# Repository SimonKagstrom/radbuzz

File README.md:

# Radbuzz
Radbuzz is an infotainment and trip computer for electric mopeds and motorcycles, targeting VESC-based
controllers. It's built for an ESP32P4 microcontroller, but can also be run on the desktop for testing.

<p align="center">

</p>
<p align="center">

</p>
<p align="center">

</p>
<p align="center">

</p>

Features:

* OpenStreetMap-based map (currently OpenCycleMap) with different zoom levels, via a GPS module
* Supports receiving Google maps/OsmAnd/etc navigation instructions via the [Gadgetbridge](https://github.com/Freeyourgadget/Gadgetbridge) app
* Speedometer, both based on VESC data and GPS
* Trip data, with average consumption, distance etc
* Tesla-style power meter bar on the right
* Trip log shown on the map, with power indicator in color
* Range estimation shown on the map
* BMS status via BLE (currently em3ev KingShark/Ali new energy BMSes)
* Incoming phone calls can accepted/declined
* SMS:es and emails are forwarded from the phone
* A menu for configuration
* Written in clean and modern C++ (C++23)

Hardware:

* [Waveshare 4.3" ESP32P4 Touch](https://www.waveshare.com/product/arduino/boards-kits/esp32-p4/esp32-p4-wifi6-touch-lcd-4.3.htm)
* A rotary encoder
* UART-based GPS (UBLOX Neo-6M / Neo-7M tested)
* A CAN-bus adapter to communicate with the VESC (a Waveshare SN65HVD230 has been used)
* A DC/DC converter to power the ESP32P4 from the 12V outlet on the VESC (a [Waveshare DC-DC buck mini module](https://www.waveshare.com/dc5-36-to-dc3v3-5.htm) used here)

the pinout for the ESP32P4 can be seen in [waveshare_p4_touch_4_3/main.cc](esp32/waveshare_p4_touch_4_3/main/main.cc)

## Setup
First install the `eim` tool (the esp-idf installation manager).

```
eim install -i v6.1
source $HOME/.espressif/tools/activate_idf_v6.1.sh
npm i lv_font_conv -g
pip3 install jinja2 pyyaml
```

## Build (target)
```
cmake -GNinja -B radbuzz_waveshare_p4_touch_4_3 -DCMAKE_BUILD_TYPE=Release <path>/radbuzz/esp32/waveshare_p4_touch_4_3
cmake --build radbuzz_waveshare_p4_touch_4_3
```

And then flash with

```
cd radbuzz_waveshare_p4_touch_4_3
ninja flash   # Or idf.py flash
```

## Build (qt/unittest)
Install the same lvgl/Python dependencies as on target:

```
npm i lv_font_conv -g
pip3 install jinja2 pyyaml
```

And then:

```
cmake -GNinja -B radbuzz_qt <path>/radbuzz/qt
cmake --build radbuzz_qt
```

or

```
cmake -GNinja -B radbuzz_unittest <path>/radbuzz/test/unittest/
cmake --build radbuzz_unittest
```

See [doc/build_instructions.md](doc/build_instructions.md) for more details on building and flashing the C6
firmware for wifi/Bluetooth.

## The OSM API key
Get an API key for thunderforest via https://www.thunderforest.com/docs/apikeys/

Put this key as a string in a `/APP_DATA/OSM_KEY.TXT` file in the root directory of this project.

A key can also be placed on the SD card, as osm_key.txt, which will be
preferred over the build time one if it exists.

## Wifi SSID
Store the SSIDs and passwords in a `/APP_DATA/SSID.TXT` file on the SD card, with
newlines. E.g.,

```
MySsid
PasswordForMySsid
OtherSsid
PasswordForOtherSsid
OpenCafeSsid

```

Leave the password line empty for open networks. The networks are stored on the
board, and the file is only imported again when its contents change.

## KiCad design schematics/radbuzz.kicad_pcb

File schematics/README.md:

## Setup for the mock script
```
pip3 install manifold3d trimesh matplotlib
```

## Generate a step file for import into onshape

```
kicad-cli pcb export step --subst-models \
    --component-filter "J*,U2,C3" \
    --user-origin 42.775x113.55mm \
    -f -o radbuzz.step radbuzz.kicad_pcb
```

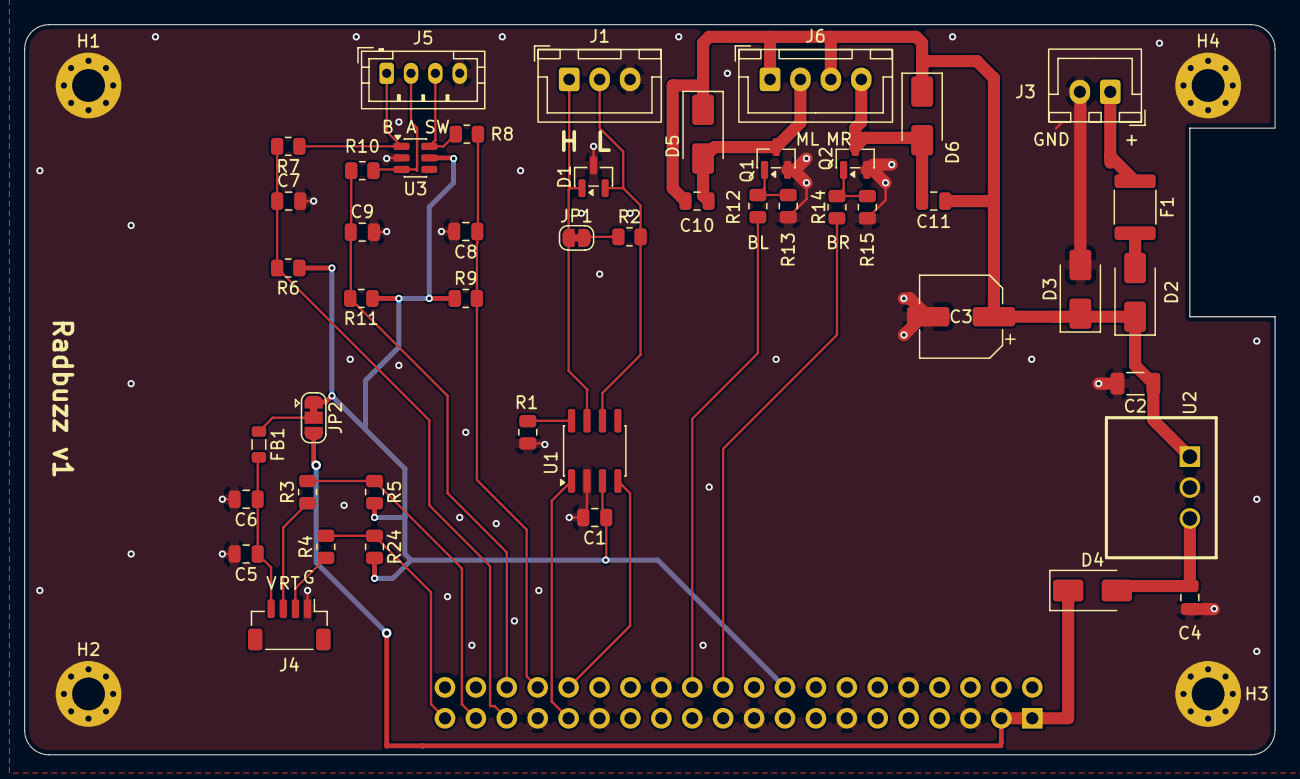
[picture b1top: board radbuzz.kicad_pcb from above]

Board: 2 copper layers, 102.8 x 60.0 mm, 52 parts (1 on the bottom side), 31 nets.

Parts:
C1, C6: 100nF; C_0805_2012Metric
C2: 10 µF/25 V X7R; C_1206_3216Metric
C3: 47 µF/35 V; CP_Elec_6.3x7.7
C4: 22 µF; C_0805_2012Metric
C5: 10µF; C_0805_2012Metric
C7, C8, C9: 10nF; C_0805_2012Metric
C10, C11: 100 nF; C_0805_2012Metric
D1: NUP2105L; SOT-23
D2, D4: SS34; D_SMA
D3: SMAJ15A; D_SMA
D5, D6: SS14; D_SMA
F1: Polyfuse 1.5 A hold, ≥24 V, 1812 size; Fuse_1812_4532Metric
FB1: 600 Ω @ 100 MHz, 0805; L_0805_2012Metric
H1, H2, H3, H4: MountingHole_Pad; MountingHole_2.7mm_M2.5_Pad_Via
J1: CAN; JST_XH_B3B-XH-A_1x03_P2.50mm_Vertical
J2: BOARD; PinHeader_2x20_P2.54mm_Vertical
J3: POWER; JST_XH_B2B-XH-A_1x02_P2.50mm_Vertical
J4: GPS; JST_SH_BM04B-SRSS-TB_1x04-1MP_P1.00mm_Vertical
J5: ROTARY_ENCODER; JST_PH_B4B-PH-K_1x04_P2.00mm_Vertical
J6: MOTOR; JST_XH_B4B-XH-A_1x04_P2.50mm_Vertical
JP1: SolderJumper_2_Bridged; SolderJumper-2_P1.3mm_Bridged_RoundedPad1.0x1.5mm
JP2: SolderJumper_3_Bridged12; SolderJumper-3_P1.3mm_Bridged12_RoundedPad1.0x1.5mm
Q1, Q2: AO3400A; SOT-23
R1: 10K; R_0805_2012Metric
R2: 120; R_0805_2012Metric
R3, R4: 220Ω; R_0805_2012Metric
R5, R6, R9, R11, R24: 10k; R_0805_2012Metric
R7, R8, R10: 1k; R_0805_2012Metric
R12, R14: 100Ω; R_0805_2012Metric
R13, R15: 100K; R_0805_2012Metric
U1: SN65HVD230; SOIC-8_3.9x4.9mm_P1.27mm
U2: K7805-2000R3
U3: SRV05-4; SOT-23-6

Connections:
+3V3: C1.1, J2.18, JP2.1 (A), R5.2, R6.1, R9.1, R11.1, R24.2, U1.3 (VCC), U3.5 (VP)
+5V: D4.1 (K), J2.1, J2.3, JP2.3 (B)
+12V: C2.1, C3.1, C10.1, C11.1, D2.1 (K), D3.1 (A1), D5.1 (K), D6.1 (K), J6.1, J6.3, U2.1 (Vin)
/Buzzer motor handling/MOTOR_L_N: C10.2, D5.2 (A), J6.2, Q1.3 (D)
/Buzzer motor handling/MOTOR_R_N: C11.2, D6.2 (A), J6.4, Q2.3 (D)
/Power/5V_PRE: C4.1, D4.2 (A), U2.3 (Vout)
/Power/VIN_FUSED: D2.2 (A), F1.2
/Power/VIN_RAW: F1.1, J3.1
BUZZ_L: J2.24, R12.2
BUZZ_R: J2.22, R14.2
CAN_RX: J2.32, U1.4 (R)
CAN_TX: J2.31, U1.1 (D)
ENC_A: C9.1, J2.36, R10.2, R11.2
ENC_B: C7.1, J2.35, R6.2, R7.2
ENC_SW: C8.1, J2.34, R8.2, R9.2
GND: C1.2, C2.2, C3.2, C4.2, C5.2, C6.2, C7.2, C8.2, C9.2, D1.3 (A), D3.2 (A2), H1.1 (1_1), H2.1 (1_1), H3.1 (1_1), H4.1 (1_1), J1.3, J2.5, J2.10, J2.13, J2.19, J2.26, J2.29, J2.33, J2.40, J3.2, J4.1, J5.4, Q1.2 (S), Q2.2 (S), R1.2, R13.1, R15.1, U1.2 (GND), U2.2 (GND), U3.2 (VN)
GPS_RX: J2.37, R3.2, R5.1
GPS_TX: J2.39, R4.2, R24.1
unnamed: D1.1 (K), J1.1, JP1.1 (A), U1.7 (CANH)
unnamed: D1.2 (K), J1.2, R2.2, U1.6 (CANL)
unnamed: J4.2, R4.1
unnamed: J4.3, R3.1
unnamed: C5.1, C6.1, FB1.2, J4.4
unnamed: J5.1, R7.1, U3.1 (IO1)
unnamed: J5.2, R10.1, U3.3 (IO2)
unnamed: J5.3, R8.1, U3.6 (IO4)
unnamed: JP1.2 (B), R2.1
unnamed: FB1.1, JP2.2 (C)
unnamed: Q1.1 (G), R12.1, R13.2
unnamed: Q2.1 (G), R14.1, R15.2
unnamed: R1.1, U1.8 (Rs)
